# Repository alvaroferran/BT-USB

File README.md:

BT-USB
===================================================================

This board is a bidirectional Bluetooth to USB bridge. It uses a BC04 bluetooth module and a LPC11u24 microcontroller programmed with Mbed. 

It is used as a bluetooth dongle to which a master can connect automatically on boot, and thus communicate with a computer without needing pairing.

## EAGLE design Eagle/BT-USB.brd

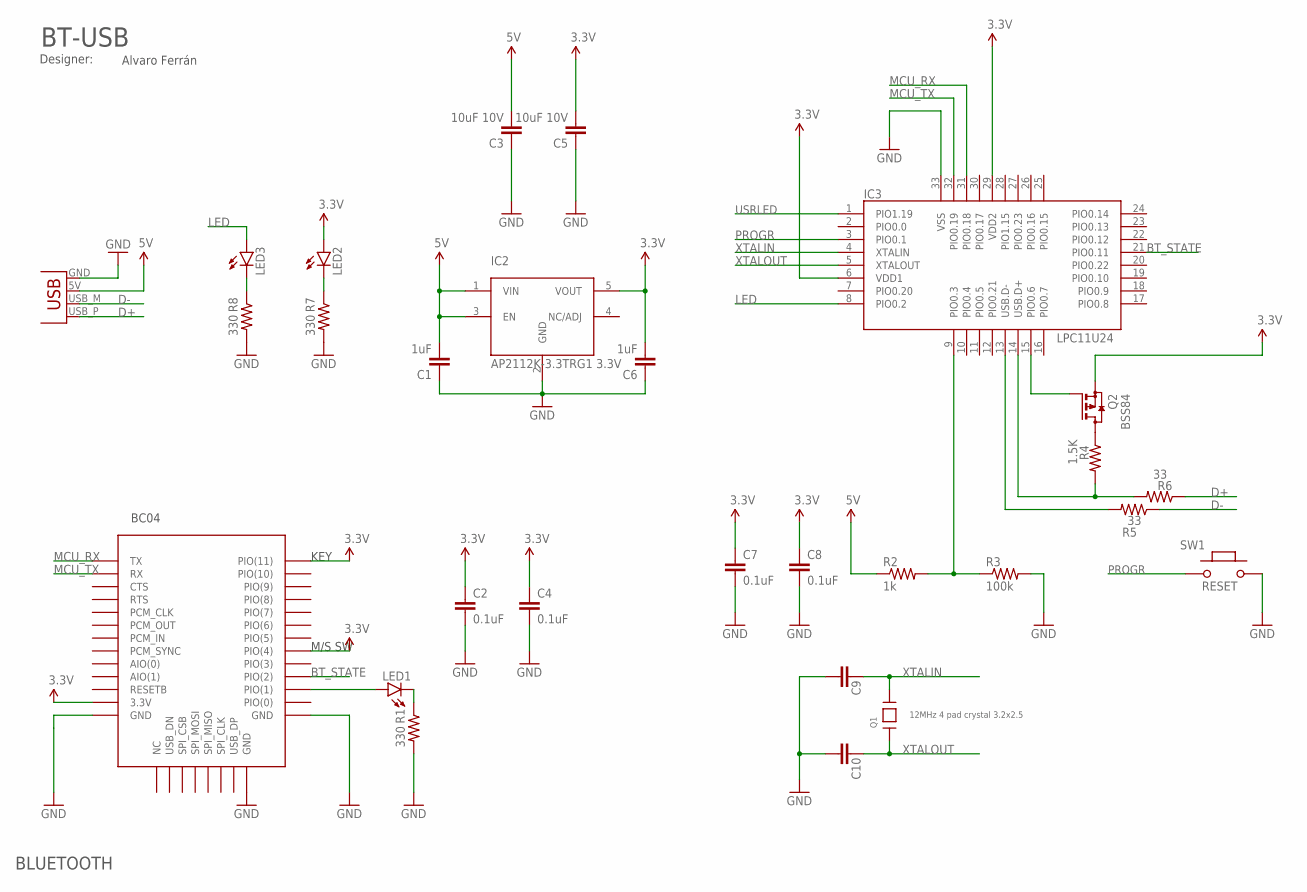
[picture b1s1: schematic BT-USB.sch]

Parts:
C1, C6: 1uF; 0402-CAP
C2, C4, C7, C8: 0.1uF; 0402-CAP
C3, C5: 10uF 10V; 0402-CAP
C9, C10: 27pF; 0402-CAP
IC1: BC04_BLUETOOTH; BC04
IC2: AP2112K-3.3TRG1 3.3V; SOT23-5
IC3: LPC11U24; HVQFN33_5X5MM
J1: USBPCB; USB-A-PCB
LED1, LED2, LED3: LED0603; LED-0603
Q1: 12MHz 4 pad crystal 3.2x2.5; CRYSTAL_3.2X2.5
Q2: BSS84; SOT23
R1, R7, R8: 330; 0402-RES
R2: 1k; 0402-RES
R3: 100k; 0402-RES
R4: 1.5K; 0402-RES
R5, R6: 33; 0402-RES
SW1: RESET; 157SW

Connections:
3.3V: C2.1, C4.1, C5.2, C6.2, C7.1, C8.1, IC1.P$12 (3.3V), IC1.P$27 (PIO(4)), IC1.P$34 (PIO(11)), IC2.5 (VOUT), IC3.6 (VDD1), IC3.29 (VDD2), LED2.A, Q2.2 (S)
5V: C1.2, C3.2, IC2.1 (VIN), IC2.3 (EN), J1.5V (VBUS), R2.1
BT_STATE: IC1.P$25 (PIO(2)), IC3.21 (PIO0.11)
D+: J1.USB_P (D+), R6.1
D-: J1.USB_M (D-), R5.1
GND: C1.1, C2.2, C3.1, C4.2, C5.1, C6.1, C7.2, C8.2, C9.2, C10.2, IC1.P$13 (GND), IC1.P$21 (GND), IC1.P$22 (GND), IC2.2 (GND), IC3.33 (VSS), J1.GND, R1.2, R3.2, R7.2, R8.2, SW1.2
LED: IC3.8 (PIO0.2), LED3.A
MCU_RX: IC1.P$1 (TX), IC3.31 (PIO0.18)
MCU_TX: IC1.P$2 (RX), IC3.32 (PIO0.19)
unnamed: IC1.P$24 (PIO(1)), LED1.A
unnamed: LED2.C, R7.1
unnamed: LED3.C, R8.1
unnamed: LED1.C, R1.1
unnamed: IC3.14 (USB.D+), R4.2, R6.2
unnamed: IC3.13 (USB.D-), R5.2
unnamed: Q2.3 (D), R4.1
unnamed: IC3.15 (PIO0.6), Q2.1 (G)
P0.3/ISP_COMMAND_USB_HIGH: IC3.9 (PIO0.3), R2.2, R3.1
PROGR: IC3.3 (PIO0.1), SW1.1
USRLED: IC3.1 (PIO1.19)
XTALIN: C9.1, IC3.4 (XTALIN), Q1.3
XTALOUT: C10.1, IC3.5 (XTALOUT), Q1.1

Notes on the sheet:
Designer:
Alvaro Ferrán
BLUETOOTH
BC04
KEY
M/S SW
BT-USB

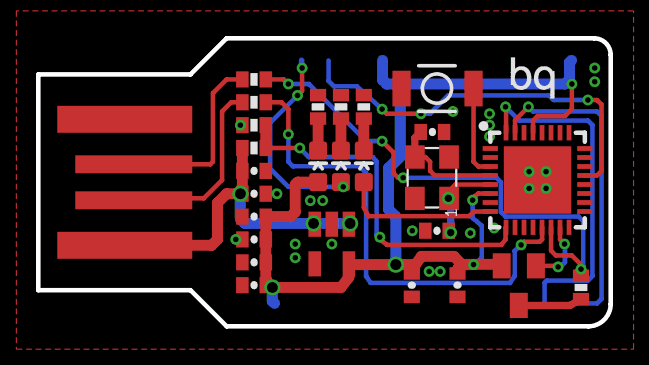
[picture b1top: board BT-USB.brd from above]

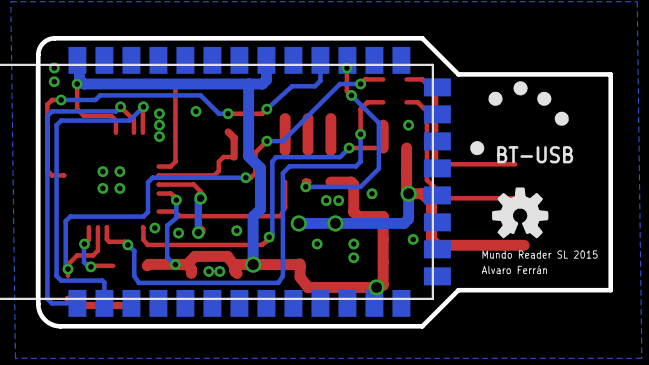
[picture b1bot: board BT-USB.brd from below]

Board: 2 copper layers, 31.8 x 16.0 mm, 31 parts (3 on the bottom side), 21 nets.

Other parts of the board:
U$1: BQ_LOGO_SMALL_1
U$2: BQ_LOGO_SMALL_2
U$3: OSHW-LOGO-S

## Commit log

2015-12-03 Project added
2016-03-14 json added

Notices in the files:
parts and their libraries:
SparkFun-Passives: Licensing: Creative Commons ShareAlike 4.0 International - https://creativecommons.org/licenses/by-sa/4.0
